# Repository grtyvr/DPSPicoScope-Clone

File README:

This is a rewrite of the HeartyGFX board using KiCad. Also the board is redone to fit into a case that I have.

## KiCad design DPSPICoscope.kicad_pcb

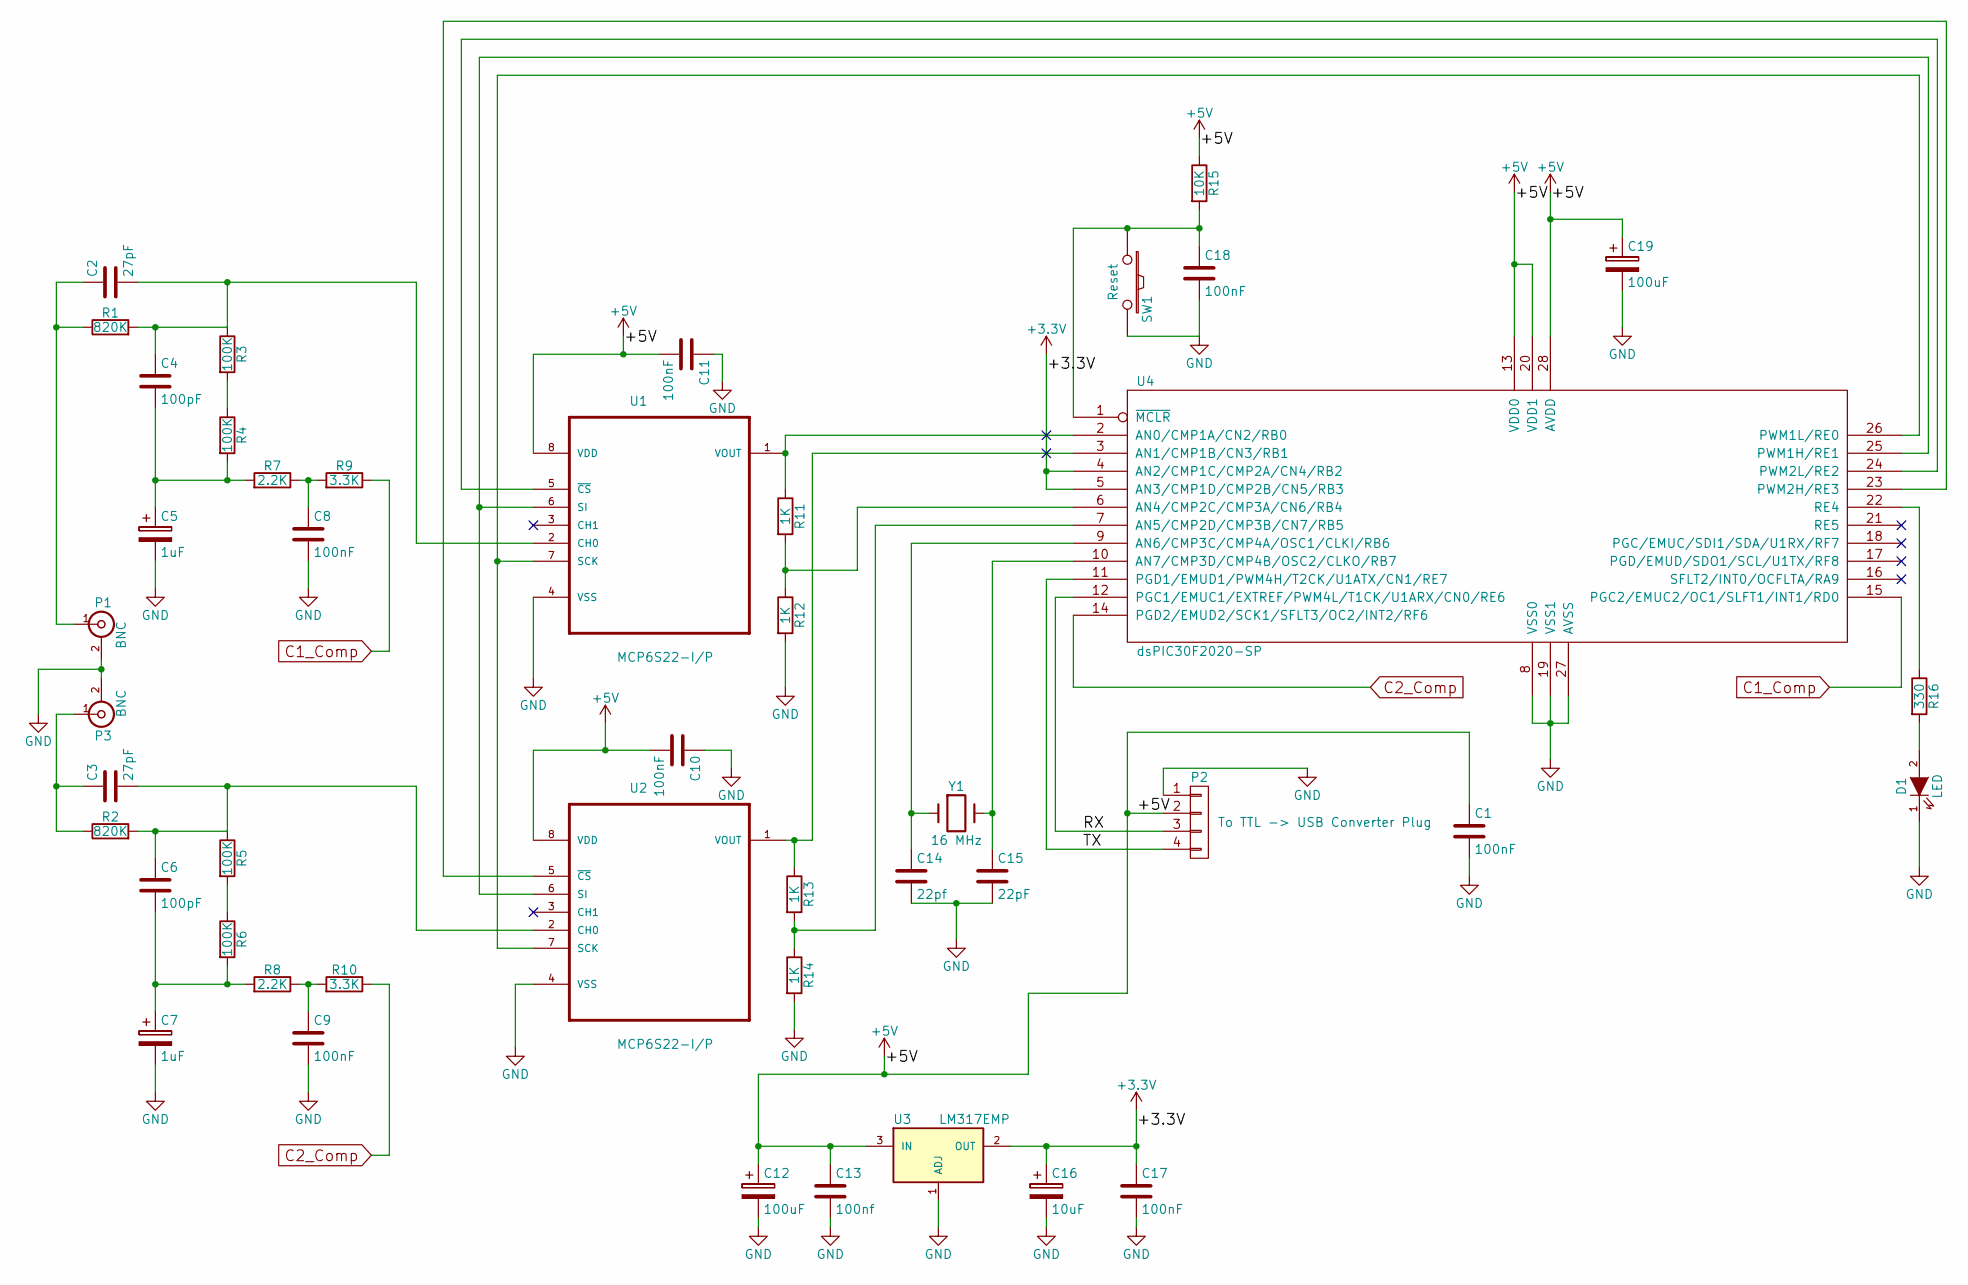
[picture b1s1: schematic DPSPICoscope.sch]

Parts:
C1, C8, C9, C10, C11, C17, C18: 100nF; C_Disc_D3_P2.5
C2, C3: 27pF; C_Disc_D3_P2.5
C4, C6: 100pF; C_Disc_D3_P2.5
C5, C7: 1uF; C_Radial_D5_L6_P2.5
C12: 100uF; C_Radial_D5_L6_P2.5
C13: 100nf; C_Disc_D3_P2.5
C14: 22pf; C_Disc_D3_P2.5
C15: 22pF; C_Disc_D3_P2.5
C16: 10uF; C_Radial_D5_L6_P2.5
C19: 100uF; C_Radial_D5_L11_P2
D1: LED; LED-5MM
P1, P3: BNC; BNC_Socket_TYCO-AMP_LargePads
P2: To TTL -> USB Converter Plug; Socket_Strip_Straight_1x04
R1, R2: 820K; Resistor_Horizontal_RM10mm
R3, R4, R5, R6: 100K; R3-5
R7, R8: 2.2K; R3-5
R9, R10: 3.3K; R3-5
R11, R12, R13, R14: 1K; R3-5
R15: 10K; R3-5
R16: 330; R3-5
SW1: Reset; SW_PUSH_SMALL
U1, U2: MCP6S22-I/P; DIP-8_W7.62mm_LongPads
U3: LM317EMP
U4: dsPIC30F2020-SP; DIP-28_W7.62mm_LongPads
Y1: 16 MHz; Crystal_HC49-U_Vertical

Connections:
+3V3: C16.1, C17.1, U3.2 (OUT), U4.4 (AN2/CMP1C/CMP2A/CN4/RB2), U4.5 (AN3/CMP1D/CMP2B/CN5/RB3)
+5V: C1.1, C10.2, C11.2, C12.1, C13.1, C19.1, P2.2, R15.1, U1.8 (VDD), U2.8 (VDD), U3.3 (IN), U4.13 (VDD0), U4.20 (VDD1), U4.28 (AVDD)
/RX: P2.3, U4.12 (PGC1/EMUC1/EXTREF/PWM4L/T1CK/U1ARX/CN0/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)
/TX: P2.4, U4.11 (PGD1/EMUD1/PWM4H/T2CK/U1ATX/CN1/RE7)
C1_Comp: R9.1, U4.15 (PGC2/EMUC2/OC1/SLFT1/INT1/RD0)
C2_Comp: R10.1, U4.14 (PGD2/EMUD2/SCK1/SFLT3/OC2/INT2/RF6)
GND: C1.2, C5.2, C7.2, C8.2, C9.2, C10.1, C11.1, C12.2, C13.2, C14.2, C15.2, C16.2, C17.2, C18.2, C19.2, D1.1 (K), P1.2 (Ext), P2.1, P3.2 (Ext), R12.2, R14.2, SW1.2, U1.4 (VSS), U2.4 (VSS), U3.1 (ADJ), U4.8 (VSS0), U4.19 (VSS1), U4.27 (AVSS)
unnamed: C2.1, P1.1 (In), R1.1
unnamed: C2.2, C4.1, R1.2, R3.1, U1.2 (CH0)
unnamed: C3.1, P3.1 (In), R2.1
unnamed: C3.2, C6.1, R2.2, R5.1, U2.2 (CH0)
unnamed: C4.2, C5.1, R4.2, R7.2
unnamed: C6.2, C7.1, R6.2, R8.2
unnamed: C8.1, R7.1, R9.2
unnamed: C9.1, R8.1, R10.2
unnamed: C14.1, U4.9 (AN6/CMP3C/CMP4A/OSC1/CLKI/RB6), Y1.1
unnamed: C15.1, U4.10 (AN7/CMP3D/CMP4B/OSC2/CLKO/RB7), Y1.2
unnamed: C18.1, R15.2, SW1.1, U4.1 (~MCLR~)
unnamed: D1.2 (A), R16.2
unnamed: R3.2, R4.1
unnamed: R5.2, R6.1
unnamed: R11.1, U1.1 (VOUT), U4.2 (AN0/CMP1A/CN2/RB0)
unnamed: R11.2, R12.1, U4.6 (AN4/CMP2C/CMP3A/CN6/RB4)
unnamed: R13.1, U2.1 (VOUT), U4.3 (AN1/CMP1B/CN3/RB1)
unnamed: R13.2, R14.1, U4.7 (AN5/CMP2D/CMP3B/CN7/RB5)
unnamed: R16.1, U4.22 (RE4)
unnamed: U1.5 (~CS), U4.24 (PWM2L/RE2)
unnamed: U1.6 (SI), U2.6 (SI), U4.25 (PWM1H/RE1)
unnamed: U1.7 (SCK), U2.7 (SCK), U4.26 (PWM1L/RE0)
unnamed: U2.5 (~CS), U4.23 (PWM2H/RE3)

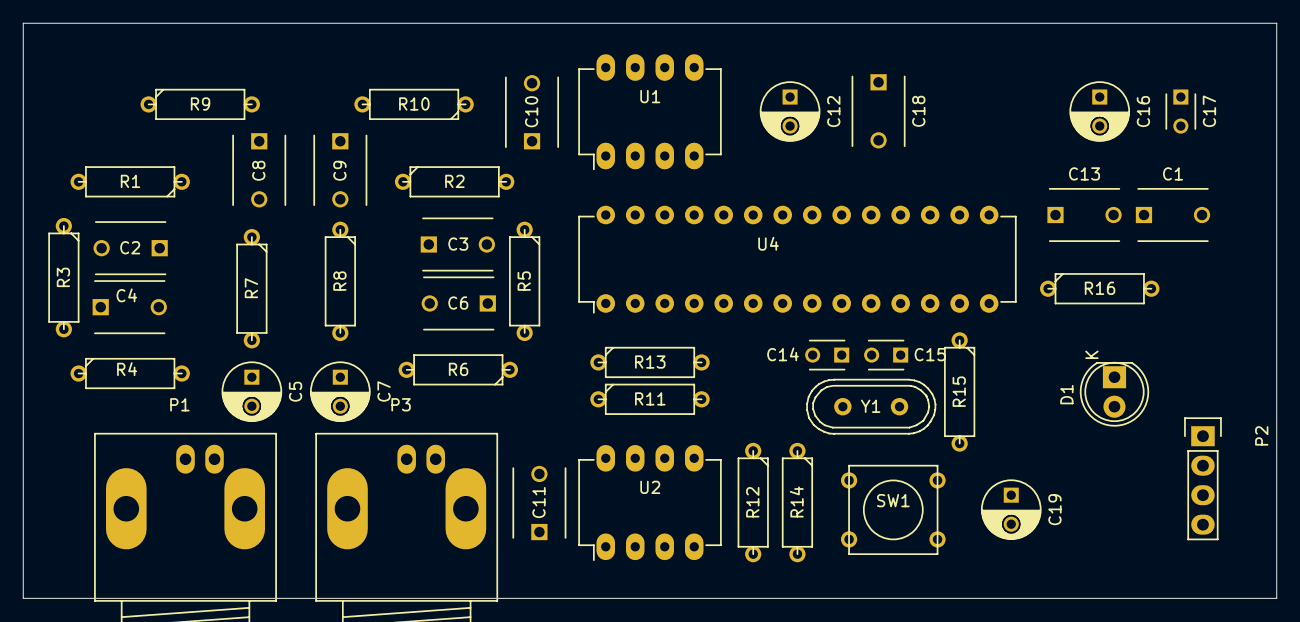
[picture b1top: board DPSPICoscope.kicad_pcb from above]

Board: 2 copper layers, 107.9 x 49.5 mm, 45 parts (1 on the bottom side), 30 nets.

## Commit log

2015-12-16 Added a readme.
2015-12-16 Added README
